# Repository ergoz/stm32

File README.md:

stm32
=====

Mine stm32 project

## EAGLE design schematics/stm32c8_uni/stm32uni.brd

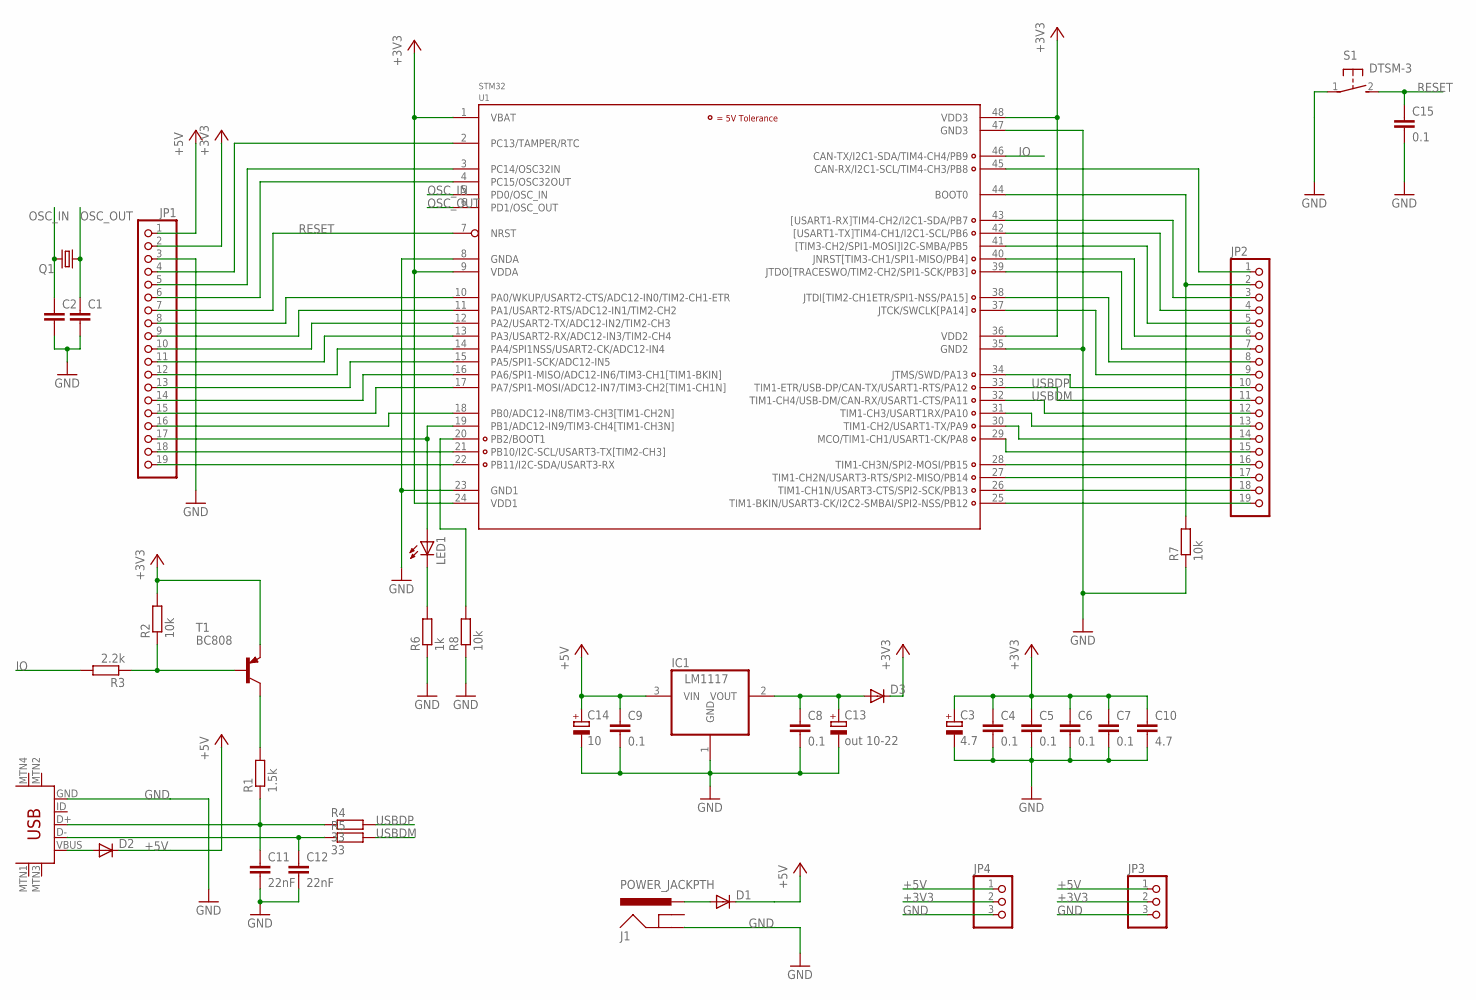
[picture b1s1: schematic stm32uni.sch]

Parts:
C1, C2: C-EUC0805; C0805
C3: 4.7; SMC_B
C4, C5, C6, C7, C8, C9, C15: 0.1; C0805
C10: 4.7; C0805
C11, C12: 22nF; C0805
C13: out 10-22; SMC_B
C14: 10; SMC_B
D1, D2, D3: DIODE-SOD123; SOD123
IC1: LM1117; SOT223
J1: POWER_JACKPTH; POWER_JACK_PTH
JP1, JP2: PINHD-1X19; 1X19
JP3, JP4: PINHD-1X3; 1X03
LED1: LEDCHIPLED_0805; CHIPLED_0805
Q1: CRYSTALHC49UP; HC49UP
R1: 1.5k; R0805
R2, R7, R8: 10k; R0805
R3: 2.2k; R0805
R4, R5: 33; R0805
R6: 1k; R0805
S1: DTSM-3
T1: BC808; SOT23-BEC
U1: STM32; LQFP48
U$1: USB-MINIB-5PIN; USB-MINIB

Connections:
+3V3: C3.+, C4.1, C5.1, C6.1, C7.1, C10.1, D3.C, JP1.2, JP3.2, JP4.2, R2.2, T1.E, U1.1 (VBAT), U1.9 (VDDA), U1.24 (VDD1), U1.36 (VDD2), U1.48 (VDD3)
+5V: C9.1, C14.+, D1.C, D2.C, IC1.3 (VIN), JP1.1, JP3.1, JP4.1
GND: C1.2, C2.2, C3.-, C4.2, C5.2, C6.2, C7.2, C8.2, C9.2, C10.2, C11.2, C12.2, C13.-, C14.-, C15.2, IC1.1 (GND), J1.GND, JP1.3, JP3.3, JP4.3, R6.1, R7.1, R8.1, S1.1, U1.8 (GNDA), U1.23 (GND1), U1.35 (GND2), U1.47 (GND3), U$1.GND
IO: R3.2, U1.46 (CAN-TX/I2C1-SDA/TIM4-CH4/PB9)
unnamed: D2.A, U$1.VBUS
unnamed: D1.A, J1.PWR
unnamed: C8.1, C13.+, D3.A, IC1.2 (VOUT)
unnamed: JP1.16, U1.18 (PB0/ADC12-IN8/TIM3-CH3[TIM1-CH2N])
unnamed: JP1.15, U1.17 (PA7/SPI1-MOSI/ADC12-IN7/TIM3-CH2[TIM1-C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)
unnamed: C11.1, R1.1, R4.1, U$1.D+
unnamed: C12.1, R5.1, U$1.D-
unnamed: R1.2, T1.C
unnamed: R2.1, R3.1, T1.B
unnamed: JP2.19, U1.25 (TIM1-BKIN/USART3-CK/I2C2-SMBAI/SPI2-NSS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)
unnamed: JP2.18, U1.26 (TIM1-CH1N/USART3-CTS/SPI2-SCK/PB13)
unnamed: JP2.17, U1.27 (TIM1-CH2N/USART3-RTS/SPI2-MISO/PB14)
unnamed: JP2.16, U1.28 (TIM1-CH3N/SPI2-MOSI/PB15)
unnamed: JP2.15, U1.29 (MCO/TIM1-CH1/USART1-CK/PA8)
unnamed: JP2.14, U1.30 (TIM1-CH2/USART1-TX/PA9)
unnamed: JP2.13, U1.31 (TIM1-CH3/USART1RX/PA10)
unnamed: JP2.10, U1.34 (JTMS/SWD/PA13)
unnamed: JP2.9, U1.37 (JTCK/SWCLK[PA14])
unnamed: JP2.8, U1.38 (JTDI[TIM2-CH1ETR/SPI1-NSS/PA15])
unnamed: JP2.7, U1.39 (JTDO[TRACESWO/TIM2-CH2/SPI1-SCK/PB3])
unnamed: JP2.6, U1.40 (JNRST[TIM3-CH1/SPI1-MISO/PB4])
unnamed: JP2.5, U1.41 ([TIM3-CH2/SPI1-MOSI]I2C-SMBA/PB5)
unnamed: JP2.4, U1.42 ([USART1-TX]TIM4-CH1/I2C1-SCL/PB6)
unnamed: JP2.3, U1.43 ([USART1-RX]TIM4-CH2/I2C1-SDA/PB7)
unnamed: JP2.2, R7.2, U1.44 (BOOT0)
unnamed: JP2.1, U1.45 (CAN-RX/I2C1-SCL/TIM4-CH3/PB8)
unnamed: JP1.19, U1.22 (PB11/I2C-SDA/USART3-RX)
unnamed: JP1.18, U1.21 (PB10/I2C-SCL/USART3-TX[TIM2-CH3])
unnamed: R8.2, U1.20 (PB2/BOOT1)
unnamed: JP1.14, U1.16 (PA6/SPI1-MISO/ADC12-IN6/TIM3-CH1[TIM1-B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)
unnamed: JP1.13, U1.15 (PA5/SPI1-SCK/ADC12-IN5)
unnamed: JP1.12, U1.14 (PA4/SPI1NSS/USART2-CK/ADC12-IN4)
unnamed: JP1.11, U1.13 (PA3/USART2-RX/ADC12-IN3/TIM2-CH4)
unnamed: JP1.10, U1.12 (PA2/USART2-TX/ADC12-IN2/TIM2-CH3)
unnamed: JP1.9, U1.11 (PA1/USART2-RTS/ADC12-IN1/TIM2-CH2)
unnamed: JP1.8, U1.10 (PA0/WKUP/USART2-CTS/ADC12-IN0/TIM2-CH1-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)
unnamed: JP1.6, U1.4 (PC15/OSC32OUT)
unnamed: JP1.5, U1.3 (PC14/OSC32IN)
unnamed: JP1.4, U1.2 (PC13/TAMPER/RTC)
unnamed: JP1.17, LED1.A, U1.19 (PB1/ADC12-IN9/TIM3-CH4[TIM1-CH3N])
unnamed: LED1.C, R6.2
OSC_IN: C2.1, Q1.2, U1.5 (PD0/OSC_IN)
OSC_OUT: C1.1, Q1.1, U1.6 (PD1/OSC_OUT)
RESET: C15.1, JP1.7, S1.2, U1.7 (NRST)
USBDM: JP2.12, R5.2, U1.32 (TIM1-CH4/USB-DM/CAN-RX/USART1-CTS/PA11)
USBDP: JP2.11, R4.2, U1.33 (TIM1-ETR/USB-DP/CAN-TX/USART1-RTS/PA12)

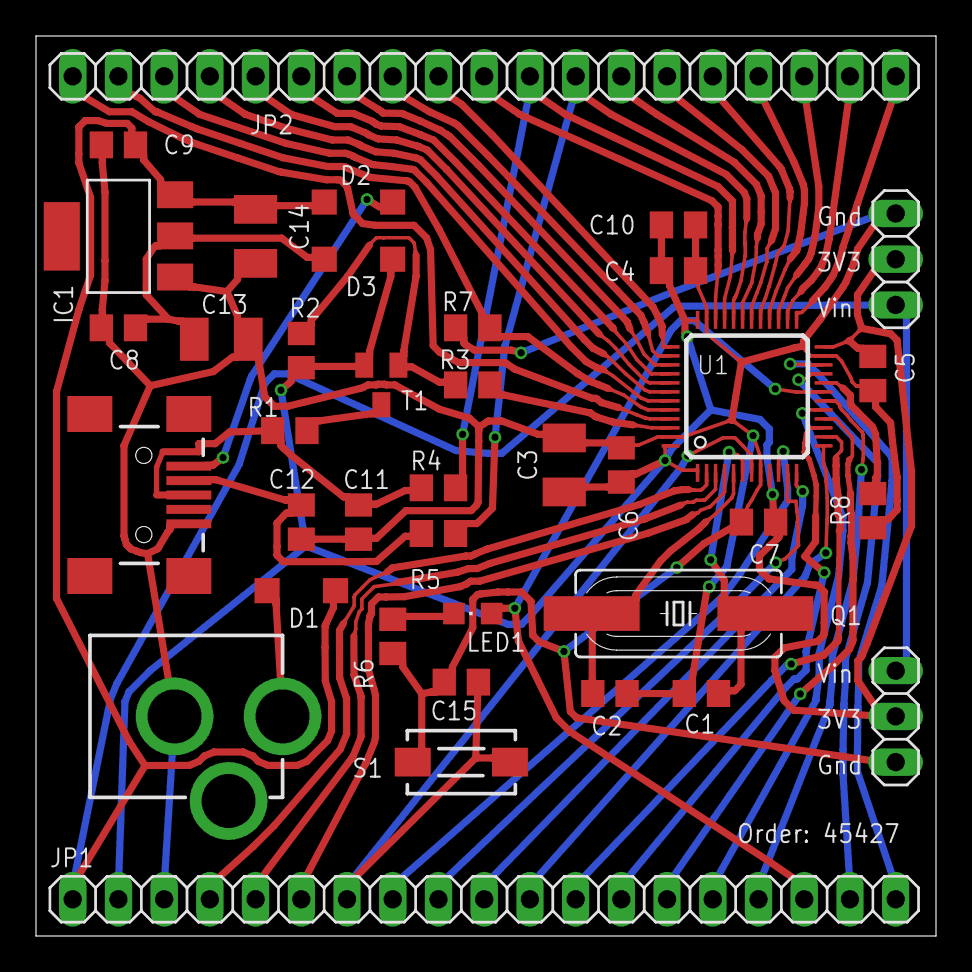
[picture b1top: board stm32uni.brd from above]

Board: 2 copper layers, 50.0 x 50.0 mm, 38 parts (0 on the bottom side), 50 nets.

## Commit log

2012-06-02 initial
2012-06-02 pictures
2012-07-07 removed junk
2012-07-07 new files
2012-07-08 save last send addr
2012-08-01 stm32 weather added
2012-08-09 modified
2012-08-09 more add
2012-08-26 NRF update Added MPL115A1 pressure Minor changes
2012-08-30 External lamp added
2012-09-11 code added

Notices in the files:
parts and their libraries:
SparkFun: Licensing: CC v3.0 Share-Alike You are welcome to use this library for commercial purposes.
